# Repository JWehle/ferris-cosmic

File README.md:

# Sweep2.1

Edited from the Ferris Sweep to clean up and add custom graphics.

## Ordering The PCB

To order the PCB the following settings are recommended<sup>1,2</sup>: 

|Detail|Value|
|---|---|
|Gerber file|`sweepv2.1_gerber.zip`|
|Base material|FR-4|
|Layers|2|
|Dimension|216.9mm x 86.9mm|
|Different design|2|
|Delivery format|Single PCB|
|PCB thickness|1.6mm|
|PCB color|(Personal preference)|
|Silkscreen|(Personal preference)|
|Surface finish|(Personal preference)|
|Outer copper weight|1oz|
|Gold Fingers|No|
|Confirm production file|No|
|Castellated holes|No|
|Remove order number|Yes|

1: Settings are for [JLCPCB](https://jlcpcb.com/), but could work for other manufacturers.

2: Settings are taken from [Kyek's video guide](https://www.youtube.com/watch?v=fBPu7AyDtkM&t=17s).

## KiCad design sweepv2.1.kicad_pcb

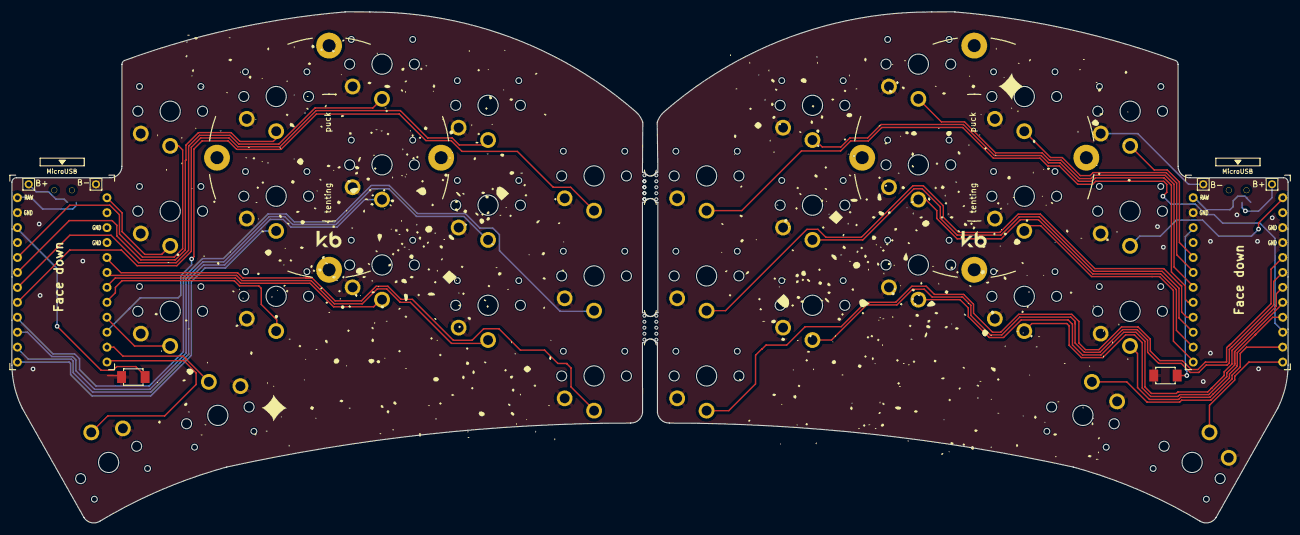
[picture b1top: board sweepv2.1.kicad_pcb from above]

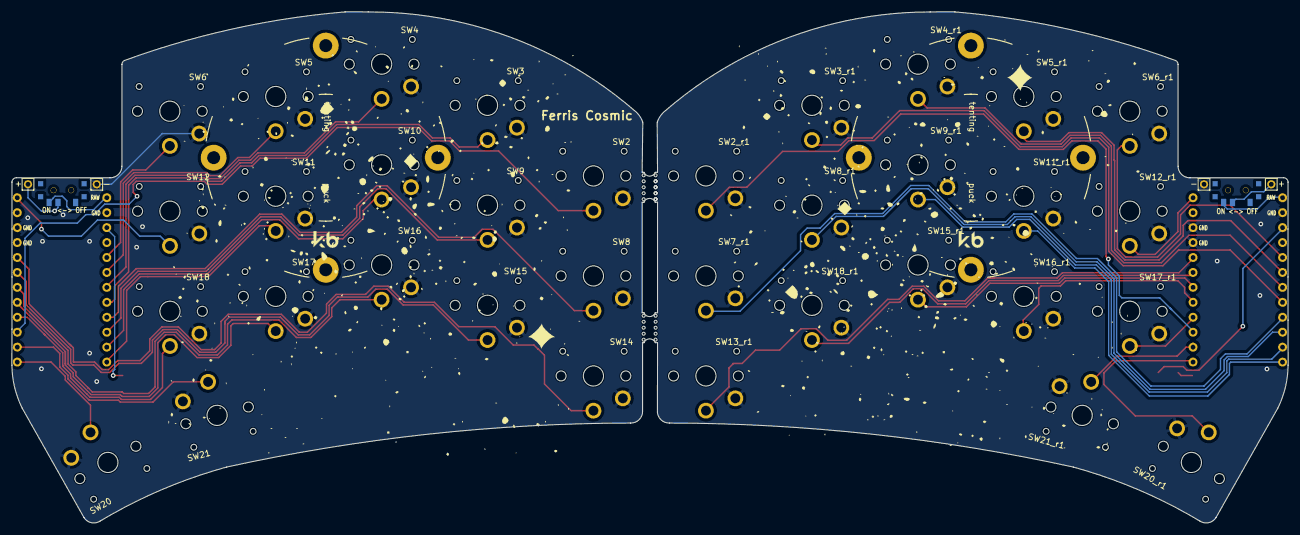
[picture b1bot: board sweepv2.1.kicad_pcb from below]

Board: 2 copper layers, 216.9 x 86.9 mm, 46 parts (2 on the bottom side), 41 nets.

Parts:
Bat+1: MountingHole_Pad; 1pin_conn
Bat+r1: MountingHole_Pad; 1pin_conn
BatGND1, BatGND4: MountingHole_Pad; 1pin_conn
RSW1, RSW2: SW_Push; Liyafy_2Pin_SMD_Micro_Switch_3x4x2mm
SW2, SW2_r1, SW3, SW3_r1, SW4, SW4_r1, SW5, SW5_r1, SW6, SW6_r1, SW7_r1, SW8, SW8_r1, SW9, SW9_r1, SW10, SW11, SW11_r1, SW12, SW12_r1, SW13_r1, SW14, SW15, SW15_r1, SW16, SW16_r1, SW17, SW17_r1, SW18, SW18_r1, SW20, SW20_r1, SW21, SW21_r1: SW_Push; kailh_low_profile_0305_sockets
SW_POWER1: SW_SPDT; SPDT_C128955
SW_POWERR1: SW_SPDT; SPDT_C128955
U1, U2: ProMicro-kbd; ProMicro_v3_min
mouse-bite-2mm-slot, mouse-bite-2mm-slot#2: VAL**; mouse-bite-5mm-slot-with-space-for-track

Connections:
BT+: Bat+1.1, SW_POWER1.2 (B)
BT+_r: Bat+r1.1, SW_POWERR1.2 (B)
Switch1: SW2.1, U1.10
Switch1_r: SW2_r1.1, U2.10
Switch2: SW3.1, U1.17
Switch2_r: SW3_r1.1, U2.17
Switch3: SW4.1, U1.18
Switch3_r: SW4_r1.1, U2.18
Switch4: SW5.1, U1.19
Switch4_r: SW5_r1.1, U2.19
Switch5: SW6.1, U1.20
Switch5_r: SW6_r1.1, U2.20
Switch6: SW8.1, U1.16
Switch6_r: SW7_r1.1, U2.16
Switch7: SW9.1, U1.15
Switch7_r: SW8_r1.1, U2.15
Switch8: SW10.1, U1.14
Switch8_r: SW9_r1.1, U2.14
Switch9: SW11.1, U1.13
Switch9_r: SW11_r1.1, U2.13
Switch10: SW12.1, U1.1
Switch10_r: SW12_r1.1, U2.1
Switch11: SW14.1, U1.5
Switch11_r: SW13_r1.1, U2.5
Switch12: SW15.1, U1.6
Switch12_r: SW18_r1.1, U2.6
Switch13: SW16.1, U1.7
Switch13_r: SW15_r1.1, U2.7
Switch14: SW17.1, U1.8
Switch14_r: SW16_r1.1, U2.8
Switch15: SW18.1, U1.9
Switch15_r: SW17_r1.1, U2.9
Switch16: SW21.1, U1.11
Switch16_r: SW21_r1.1, U2.11
Switch17: SW20.1, U1.12
Switch17_r: SW20_r1.1, U2.12
gnd: BatGND1.1, BatGND4.1, RSW1.1, RSW2.1, SW2.2, SW2_r1.2, SW3.2, SW3_r1.2, SW4.2, SW4_r1.2, SW5.2, SW5_r1.2, SW6.2, SW6_r1.2, SW7_r1.2, SW8.2, SW8_r1.2, SW9.2, SW9_r1.2, SW10.2, SW11.2, SW11_r1.2, SW12.2, SW12_r1.2, SW13_r1.2, SW14.2, SW15.2, SW15_r1.2, SW16.2, SW16_r1.2, SW17.2, SW17_r1.2, SW18.2, SW18_r1.2, SW20.2, SW20_r1.2, SW21.2, SW21_r1.2, U1.3, U1.4, U1.23, U2.3, U2.4, U2.23
raw: SW_POWER1.3 (C), SW_POWERR1.3 (C), U1.24, U2.24
reset: RSW1.2, U1.22
reset_r: RSW2.2, U2.22
vcc: U1.21, U2.21

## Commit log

2025-01-25 remove old footprint
2025-01-26 layout finishing touches
2025-01-26 final gerbers and order
2025-02-17 new layout edits for 0305 sockets
